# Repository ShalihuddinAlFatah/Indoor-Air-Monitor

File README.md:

# Indoor-Air-Monitor
#How it works:
It measures temperature, humidity, and some gases in PPM (LPG, CO (carbon monoxide), and smoke). 
Print those data to the LCD and send the data to the UDP server. It uses ESP8266 (NodeMCU ESP-12E dev board) to acquire data from the sensors.
This project consist of schematic and PCB layout files (KiCad), Arduino sketch for NodeMCU esp-12e, and Dashboard app for Windows PC.
The dashboard app developed using C# language in Visual Studio Community 2022. 

*UDP server means any Windows OS computer which has support for UDP protocol

#Dashboard app:
The dashboard app has an 'advanced UI' :P. You cant move the window by dragging random stuff.
Click, hold and drag the 'L' button to move the window. Click 'M' button to minimize the window.
Click 'X' button to close the window.

#How to pair a UDP server (MUST BE IN THIS ORDER, to make it easier :D):
1. Open the dashboard app. Click 'Pair' and a new window will appear.
2. Enter the UDP server's local IP address.
3. Connect the device to the UDP server using a USB cable. 
4. Click 'Scan' to scan all the active COM ports on the UDP server.
5. Choose the proper COM port to which the device connects.
6. Click 'Pair' to send the UDP server's local IP address to the device.

*The device automatically enters the pairing mode every time it is powered on.
*The pairing mode lasts 30 seconds, so you must complete steps 3 to 6 within 30 seconds.
*The device must be in the same network as the UDP server.

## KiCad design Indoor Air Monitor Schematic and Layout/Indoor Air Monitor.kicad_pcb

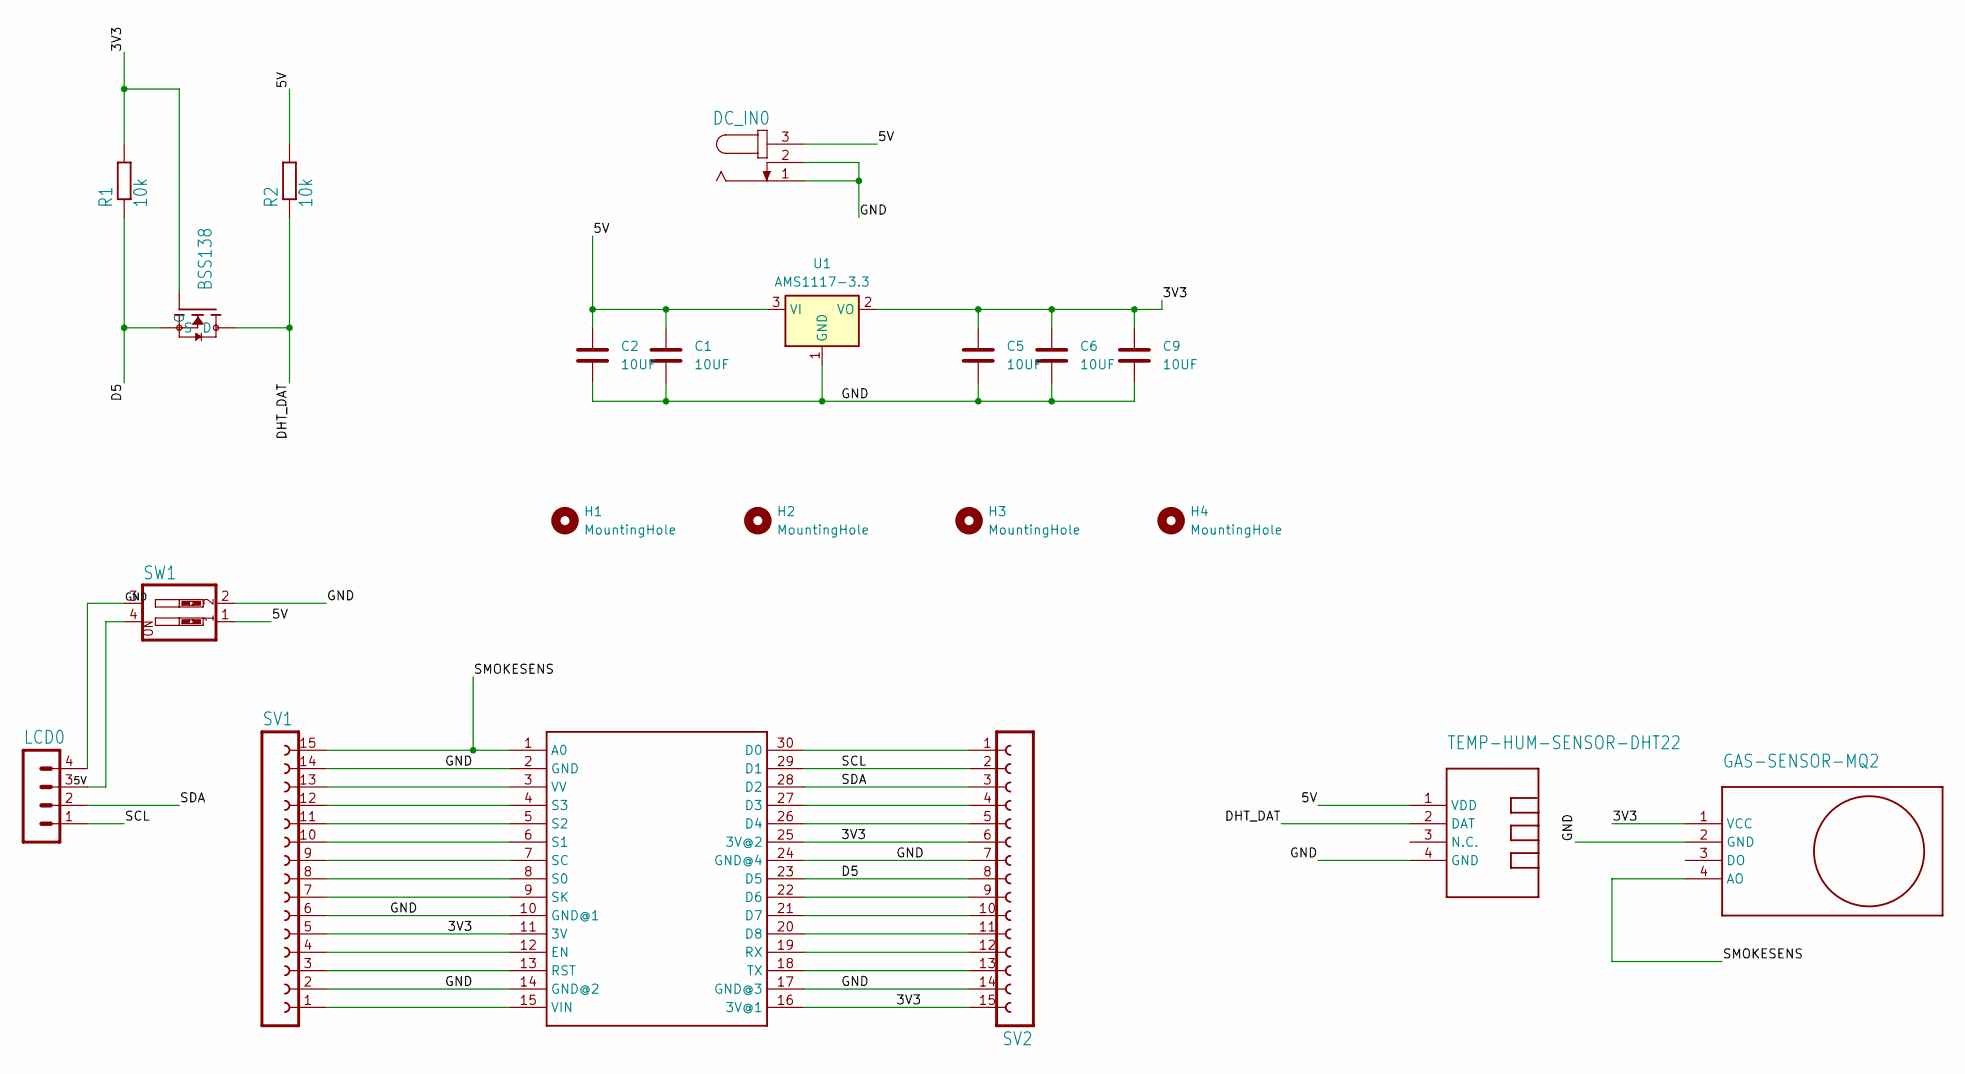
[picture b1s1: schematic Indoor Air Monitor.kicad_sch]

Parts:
C1, C2, C5, C6, C9: 10UF; C_0805_2012Metric_Pad1.18x1.45mm_HandSolder
DC_IN0: JACK-PLUG0; SPC4077
H1, H2, H3, H4: MountingHole; MountingHole_3.2mm_M3_DIN965_Pad
LCD0: MA04-1
R1, R2: 10k; R0805
SV1, SV2: FE15-1; FE15
SW1: SW_DIP-2; EDG-02
U1: AMS1117-3.3; SOT-223-3_TabPin2
U$1: NODEMCU
U$2: TEMP-HUM-SENSOR-DHT22
U$3: GAS-SENSOR-MQ2
U$4: BSS138

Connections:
/3V3: C5.1, C6.1, C9.1, R1.2, SV1.5, SV2.6, SV2.15, U1.2 (VO), U$1.11 (3V), U$1.16 (3V@1), U$1.25 (3V@2), U$3.1 (VCC), U$4.G
/5V: C1.1, C2.1, DC_IN0.3, LCD0.3, R2.2, SW1.1, SW1.4, U1.3 (VI), U$2.1 (VDD)
/D5: R1.1, SV2.8, U$1.23 (D5), U$4.S
/DHT_DAT: R2.1, U$2.2 (DAT), U$4.D
/GND: C1.2, C2.2, C5.2, C6.2, C9.2, DC_IN0.1, DC_IN0.2, LCD0.4, SV1.2, SV1.6, SV1.14, SV2.7, SV2.14, SW1.2, SW1.3, U1.1 (GND), U$1.2 (GND), U$1.10 (GND@1), U$1.14 (GND@2), U$1.17 (GND@3), U$1.24 (GND@4), U$2.4 (GND), U$3.2 (GND)
/SCL: LCD0.1, SV2.2, U$1.29 (D1)
/SDA: LCD0.2, SV2.3, U$1.28 (D2)
/SMOKESENS: SV1.15, U$1.1 (A0), U$3.4 (AO)
unnamed: SV2.1, U$1.30 (D0)
unnamed: SV2.4, U$1.27 (D3)
unnamed: SV2.5, U$1.26 (D4)
unnamed: SV2.9, U$1.22 (D6)
unnamed: SV2.10, U$1.21 (D7)
unnamed: SV2.11, U$1.20 (D8)
unnamed: SV1.4, U$1.12 (EN)
unnamed: SV1.3, U$1.13 (RST)
unnamed: SV2.12, U$1.19 (RX)
unnamed: SV1.8, U$1.8 (S0)
unnamed: SV1.10, U$1.6 (S1)
unnamed: SV1.11, U$1.5 (S2)
unnamed: SV1.12, U$1.4 (S3)
unnamed: SV1.9, U$1.7 (SC)
unnamed: SV1.7, U$1.9 (SK)
unnamed: SV2.13, U$1.18 (TX)
unnamed: SV1.1, U$1.15 (VIN)
unnamed: SV1.13, U$1.3 (VV)

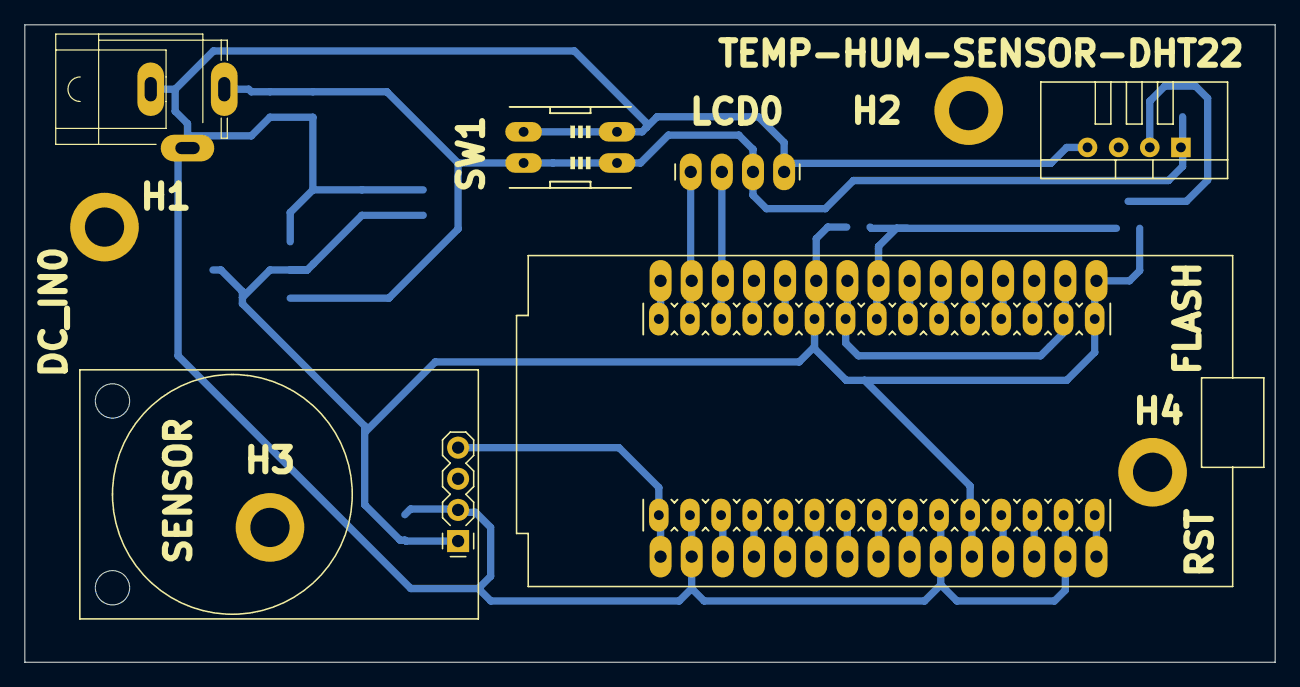
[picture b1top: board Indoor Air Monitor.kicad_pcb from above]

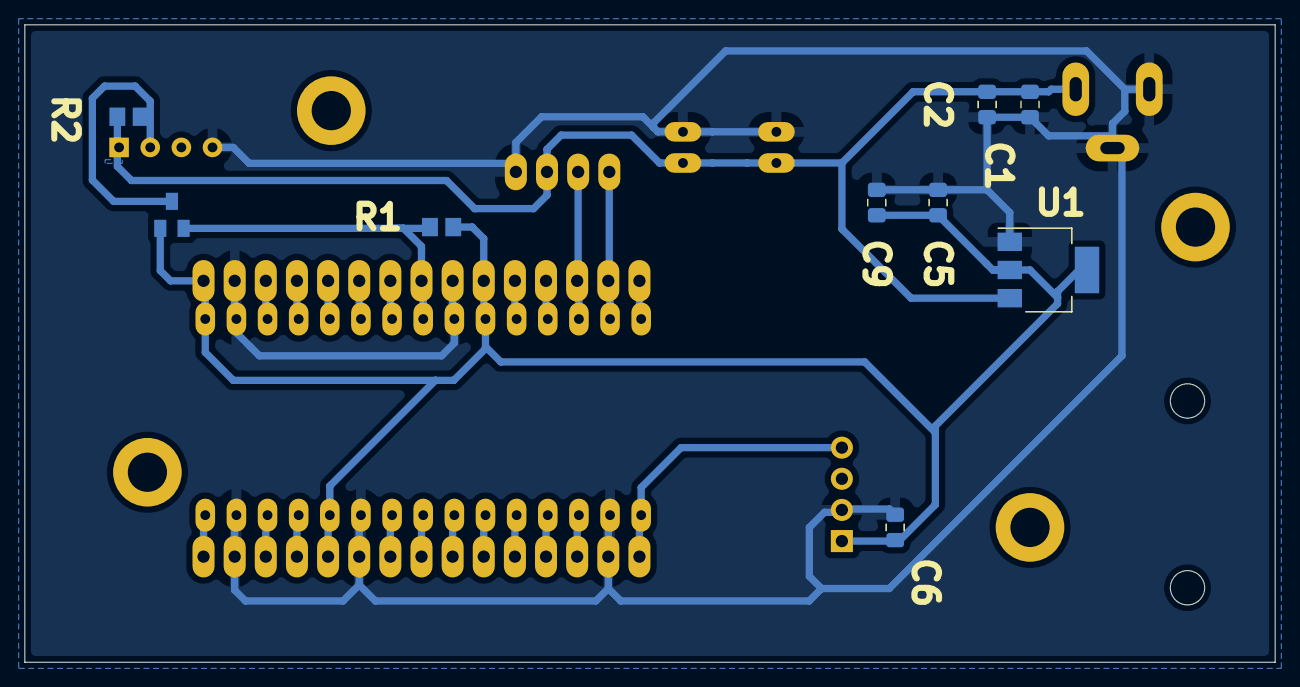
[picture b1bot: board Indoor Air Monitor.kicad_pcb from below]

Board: 2 copper layers, 102.0 x 52.0 mm, 21 parts (9 on the bottom side), 26 nets.

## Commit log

2025-02-22 Update LICENSE
2025-02-24 Add some project photos
2025-02-24 Rename 20241121_142315.jpg to The Device.jpg
2025-02-24 Rename 20241121_142500.jpg to The Dashboard App.jpg
2025-03-03 New Arduino sketch
    Just make the Arduino sketch more modular
